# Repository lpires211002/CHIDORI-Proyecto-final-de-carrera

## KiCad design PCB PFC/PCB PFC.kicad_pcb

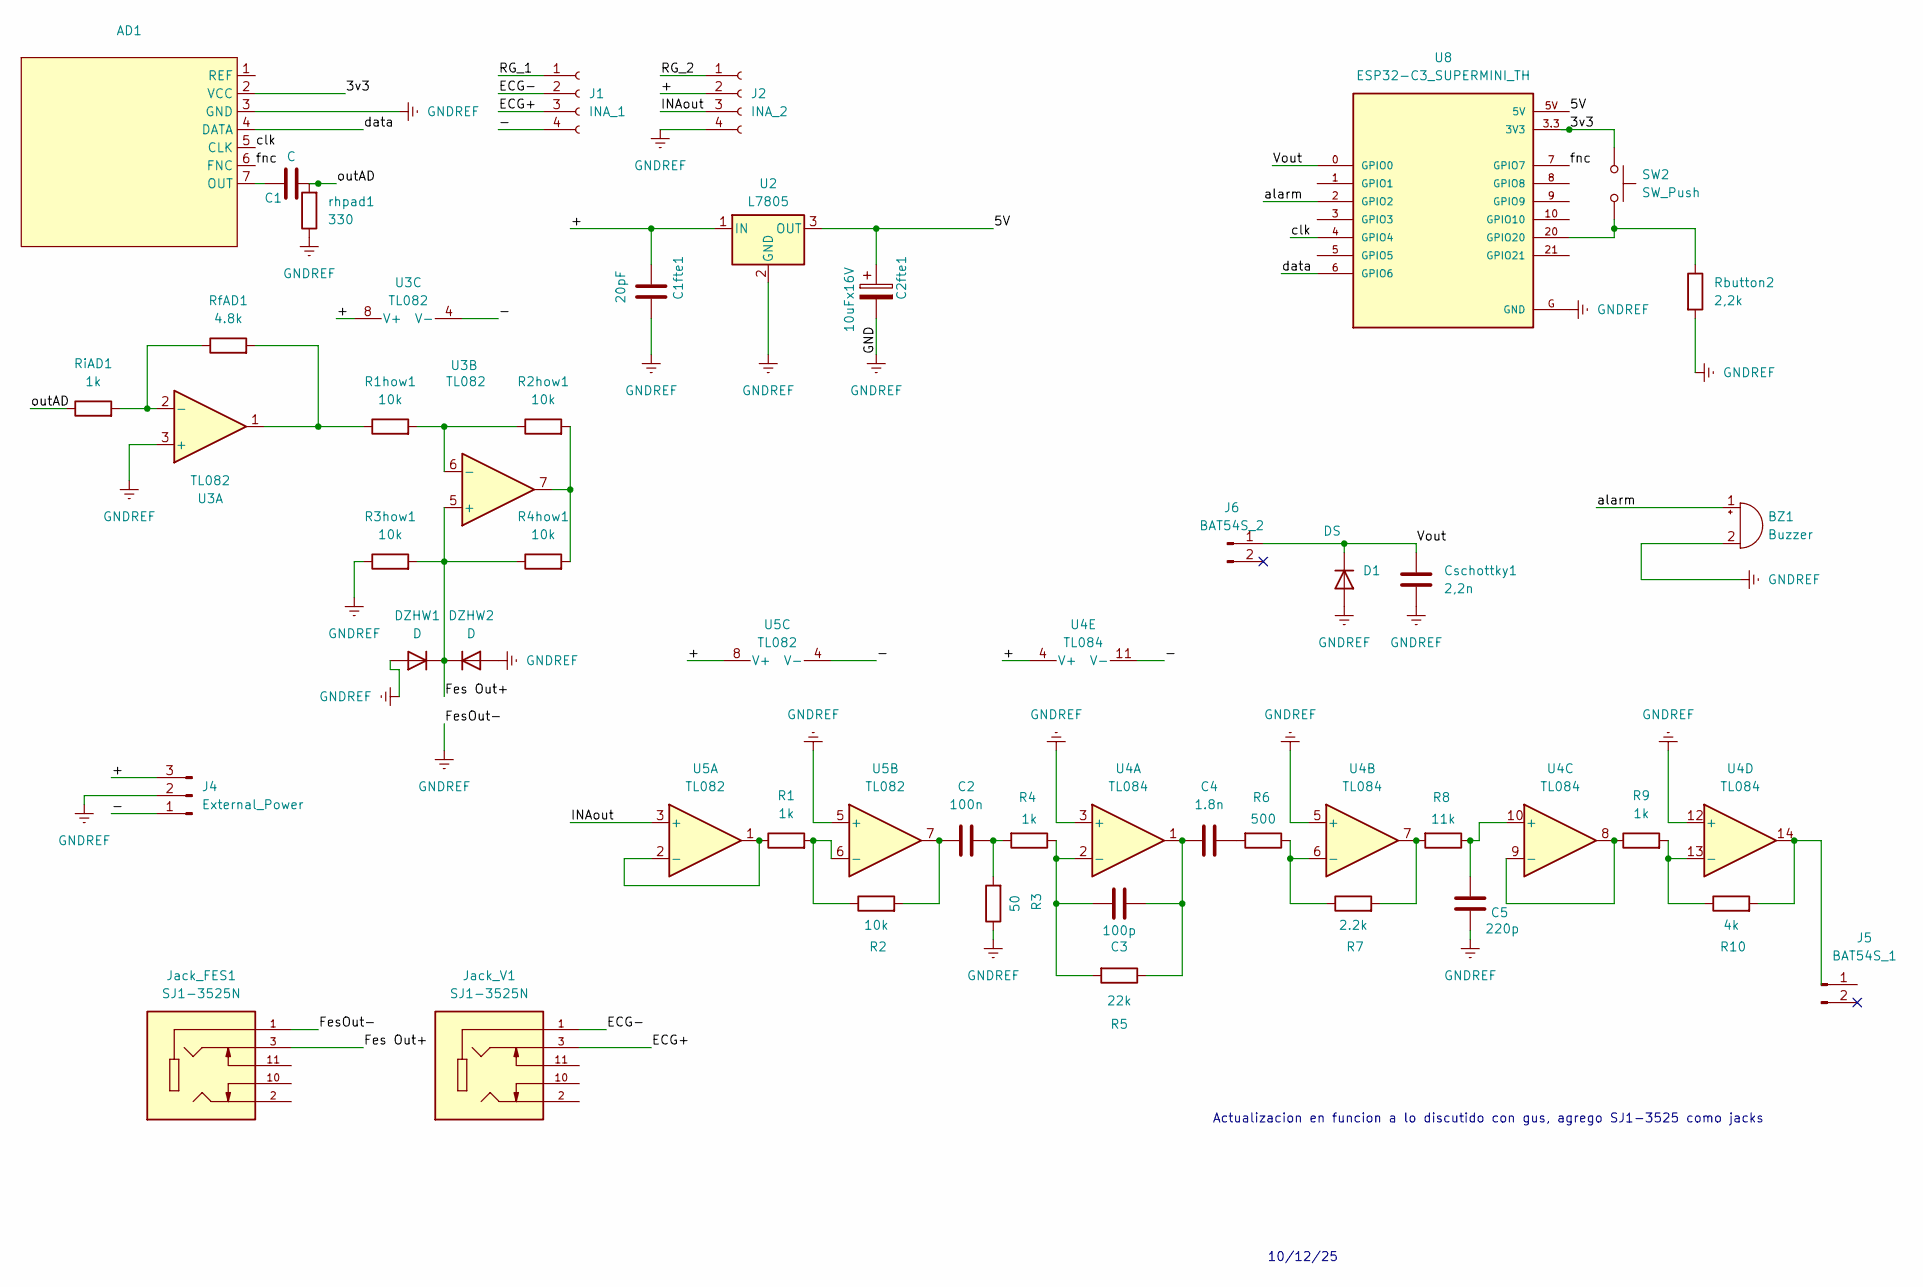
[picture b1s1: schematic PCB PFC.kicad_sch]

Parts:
AD1: AD9833
BZ1: Buzzer; Buzzer_12x9.5RM7.6
C1: C; C_Disc_D5.0mm_W2.5mm_P2.50mm
C1fte1: 20pF; C_Disc_D5.0mm_W2.5mm_P2.50mm
C2: 100n; C_Disc_D5.0mm_W2.5mm_P2.50mm
C2fte1: 10uFx16V; CP_Radial_D5.0mm_P2.50mm
C3: 100p; C_Disc_D5.0mm_W2.5mm_P2.50mm
C4: 1.8n; C_Disc_D5.0mm_W2.5mm_P2.50mm
C5: 220p; C_Disc_D5.0mm_W2.5mm_P2.50mm
Cschottky1: 2,2n; C_Disc_D5.0mm_W2.5mm_P2.50mm
D1: DS; D_DO-35_SOD27_P7.62mm_Horizontal
DZHW1, DZHW2: D; D_DO-35_SOD27_P7.62mm_Horizontal
J1: INA_1; PinSocket_1x04_P2.54mm_Vertical
J2: INA_2; PinSocket_1x04_P2.54mm_Vertical
J4: External_Power; JST_EH_B3B-EH-A_1x03_P2.50mm_Vertical
J5: BAT54S_1; PinSocket_1x02_P2.54mm_Vertical
J6: BAT54S_2; PinSocket_1x02_P2.54mm_Vertical
Jack_FES1: SJ1-3525N; CUI_SJ1-3525N; PARTREV 1.05
Jack_V1: SJ1-3525N; CUI_SJ1-3525N; PARTREV 1.05
R1, R4, R9: 1k; R_Axial_DIN0204_L3.6mm_D1.6mm_P7.62mm_Horizontal
R1how1, R2, R2how1, R3how1, R4how1: 10k; R_Axial_DIN0204_L3.6mm_D1.6mm_P7.62mm_Horizontal
R3: 50; R_Axial_DIN0204_L3.6mm_D1.6mm_P7.62mm_Horizontal
R5: 22k; R_Axial_DIN0204_L3.6mm_D1.6mm_P7.62mm_Horizontal
R6: 500; R_Axial_DIN0204_L3.6mm_D1.6mm_P7.62mm_Horizontal
R7: 2.2k; R_Axial_DIN0204_L3.6mm_D1.6mm_P7.62mm_Horizontal
R8: 11k; R_Axial_DIN0204_L3.6mm_D1.6mm_P7.62mm_Horizontal
R10: 4k; R_Axial_DIN0204_L3.6mm_D1.6mm_P7.62mm_Horizontal
Rbutton2: 2,2k; R_Axial_DIN0204_L3.6mm_D1.6mm_P7.62mm_Horizontal
RfAD1: 4.8k; R_Axial_DIN0204_L3.6mm_D1.6mm_P7.62mm_Horizontal
RiAD1: 1k; R_Axial_DIN0204_L3.6mm_D1.6mm_P7.62mm_Horizontal
SW2: SW_Push; SW_PUSH_6mm
U2: L7805; TO-220-3_Vertical
U3, U5: TL082; DIP-8_W7.62mm
U4: TL084; DIP-14_W7.62mm
U8: ESP32-C3_SUPERMINI_TH; MODULE_ESP32-C3_SUPERMINI_TH
rhpad1: 330; R_Axial_DIN0204_L3.6mm_D1.6mm_P7.62mm_Horizontal

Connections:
/3v3: AD1.2 (VCC), SW2.1, U8.3.3 (3V3)
/5V: C2fte1.1, U2.3 (OUT), U8.5V
/+: C1fte1.1, J2.2, J4.3, U2.1 (IN), U3.8 (V+), U4.4 (V+), U5.8 (V+)
/-: J1.4, J4.1, U3.4 (V-), U4.11 (V-), U5.4 (V-)
/ECG+: J1.3, Jack_V1.3
/ECG-: J1.2, Jack_V1.1
/Fes Out+: DZHW1.1 (K), DZHW2.1 (K), Jack_FES1.3, R3how1.2, R4how1.1, U3.5 (+)
/INAout: J2.3, U5.3 (+)
/RG_1: J1.1
/RG_2: J2.1
/Vout: Cschottky1.2, D1.1 (K), J6.1, U8.0 (GPIO0)
/alarm: BZ1.1 (+), U8.2 (GPIO2)
/clk: AD1.5 (CLK), U8.4 (GPIO4)
/data: AD1.4 (DATA), U8.6 (GPIO6)
/fnc: AD1.6 (FNC), U8.7 (GPIO7)
/outAD: C1.2, RiAD1.1, rhpad1.2
GNDREF: AD1.3 (GND), BZ1.2 (-), C1fte1.2, C2fte1.2, C5.1, Cschottky1.1, D1.2 (A), DZHW1.2 (A), DZHW2.2 (A), J2.4, J4.2, Jack_FES1.1, R3.1, R3how1.1, Rbutton2.2, U2.2 (GND), U3.3 (+), U4.3 (+), U4.5 (+), U4.12 (+), U5.5 (+), U8.G (GND), rhpad1.1
unnamed: AD1.7 (OUT), C1.1
unnamed: C2.1, R2.2, U5.7
unnamed: C2.2, R3.2, R4.2
unnamed: C3.2, C4.1, R5.1, U4.1
unnamed: C4.2, R6.2
unnamed: R1how1.1, RfAD1.2, U3.1
unnamed: R2how1.2, R4how1.2, U3.7
unnamed: R7.2, R8.2, U4.7
unnamed: R10.2, U4.14
unnamed: RfAD1.1, RiAD1.2, U3.2 (-)
unnamed: R1how1.2, R2how1.1, U3.6 (-)
unnamed: C3.1, R4.1, R5.2, U4.2 (-)
unnamed: R6.1, R7.1, U4.6 (-)
unnamed: C5.2, R8.1, U4.10 (+)
unnamed: R9.1, U4.8, U4.9 (-)
unnamed: R9.2, R10.1, U4.13 (-)
unnamed: R1.1, U5.1, U5.2 (-)
unnamed: R1.2, R2.1, U5.6 (-)
unnamed: Rbutton2.1, SW2.2, U8.20 (GPIO20)

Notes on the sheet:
10/12/25
Actualizacion en funcion a lo discutido con gus, agrego SJ1-3525 como jacks

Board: 2 copper layers, 44 parts (0 on the bottom side), 34 nets, no tracks yet.

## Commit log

2025-11-12 Primer commit
2025-11-26 Rediseño de UI y organización de carpetas
2025-11-27 Agrego UI mas fachera
2025-11-28 Correcciones y organizacion
2025-12-10 Agrego jacks de ECG y librerias
2025-12-11 Cambios al LTSPICE
2025-12-13 Purga de .ino y correcciones de Js
